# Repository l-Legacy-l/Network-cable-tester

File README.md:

# Network-cable-tester
This project was carried out in the first year of a bachelor's degree in computer science at the Haute école en Hainaut.

The purpose of the project is to check the operating status of a network cable (RJ45).
The cable tester includes the LED module and the PIC module. 
2 versions of the PCB have been made, the first one allows to be engraved only in single layer and the second one in double layer (space saving) .

In terms of PIC programming (PIC16F628A), 3 modes have been implemented: 
1. a short press of the button switches to the next LED
2. a long press speeds up the process by automatically switching to the following LED
3. a longer press lights up all the LEDs at the same time

# Usage

You can test the project with the Proteus simulation software and the right cabling.

You can also try it in real with a breadboard, the right hardware and MPlab software to upload the code into the PIC.

You must use the compiled file NetworkCableTester.hex

For more information, you can consult the report detailing the software and hardware used and more detailed explanations (in French).

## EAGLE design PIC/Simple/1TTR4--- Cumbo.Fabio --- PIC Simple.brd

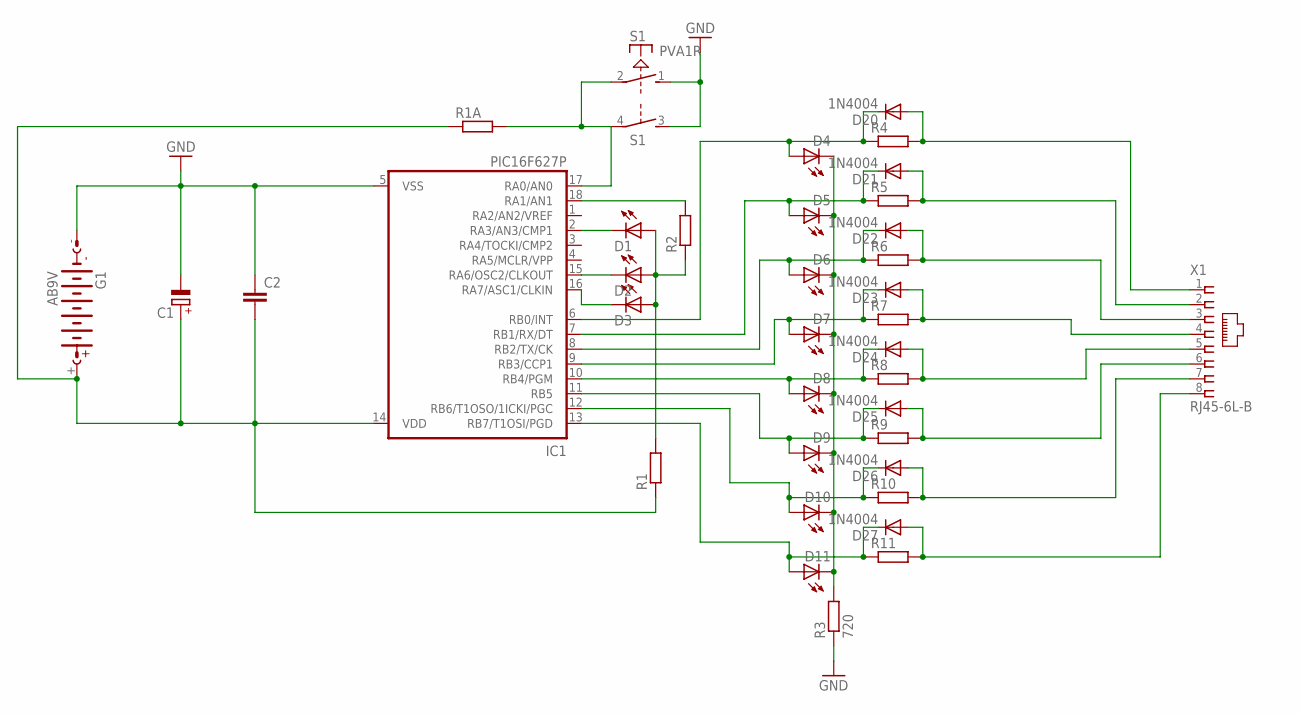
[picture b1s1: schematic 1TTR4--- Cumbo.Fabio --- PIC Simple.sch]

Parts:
C1: CPOL-EUE5-6; E5-6
C2: C-EU050-024X044; C050-024X044
D1, D2, D3, D4, D5, D6, D7, D8, D9, D10, D11: LED5MM
D20, D21, D22, D23, D24, D25, D26, D27: 1N4004; DO41-10
G1: AB9V
IC1: PIC16F627P; DIL18
R1, R1A, R2, R4, R5, R6, R7, R8, R9, R10, R11: R-EU_0204/7; 0204/7
R3: 720; 0204/7
S1: PVA1R
X1: RJ45-6L-B; RJ45-NO-SHIELD

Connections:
GND: C1.-, C2.1, G1.-, IC1.5 (VSS), R3.1, S1.1 (S), S1.3 (S)
unnamed: D11.A, D27.C, IC1.13 (RB7/T1OSI/PGD), R11.1
unnamed: D27.A, R11.2, X1.8
unnamed: D10.A, D26.C, IC1.12 (RB6/T1OSO/1ICKI/PGC), R10.1
unnamed: D9.A, D25.C, IC1.11 (RB5), R9.1
unnamed: D24.A, R8.2, X1.5
unnamed: D23.A, R7.2, X1.4
unnamed: D22.A, R6.2, X1.3
unnamed: D21.A, R5.2, X1.2
unnamed: D20.A, R4.2, X1.1
unnamed: D1.K (C), IC1.2 (RA3/AN3/CMP1)
unnamed: D25.A, R9.2, X1.6
unnamed: D7.A, D23.C, IC1.9 (RB3/CCP1), R7.1
unnamed: D26.A, R10.2, X1.7
unnamed: D6.A, D22.C, IC1.8 (RB2/TX/CK), R6.1
unnamed: D5.A, D21.C, IC1.7 (RB1/RX/DT), R5.1
unnamed: D4.A, D20.C, IC1.6 (RB0/INT), R4.1
unnamed: D4.K (C), D5.K (C), D6.K (C), D7.K (C), D8.K (C), D9.K (C), D10.K (C), D11.K (C), R3.2
unnamed: C1.+, C2.2, G1.+, IC1.14 (VDD), R1.1, R1A.1
unnamed: IC1.17 (RA0/AN0), R1A.2, S1.2, S1.4
unnamed: D8.A, D24.C, IC1.10 (RB4/PGM), R8.1
unnamed: D3.K (C), IC1.16 (RA7/ASC1/CLKIN)
unnamed: D2.K (C), IC1.15 (RA6/OSC2/CLKOUT)
unnamed: IC1.18 (RA1/AN1), R2.2
unnamed: D1.A, D2.A, D3.A, R1.2, R2.1

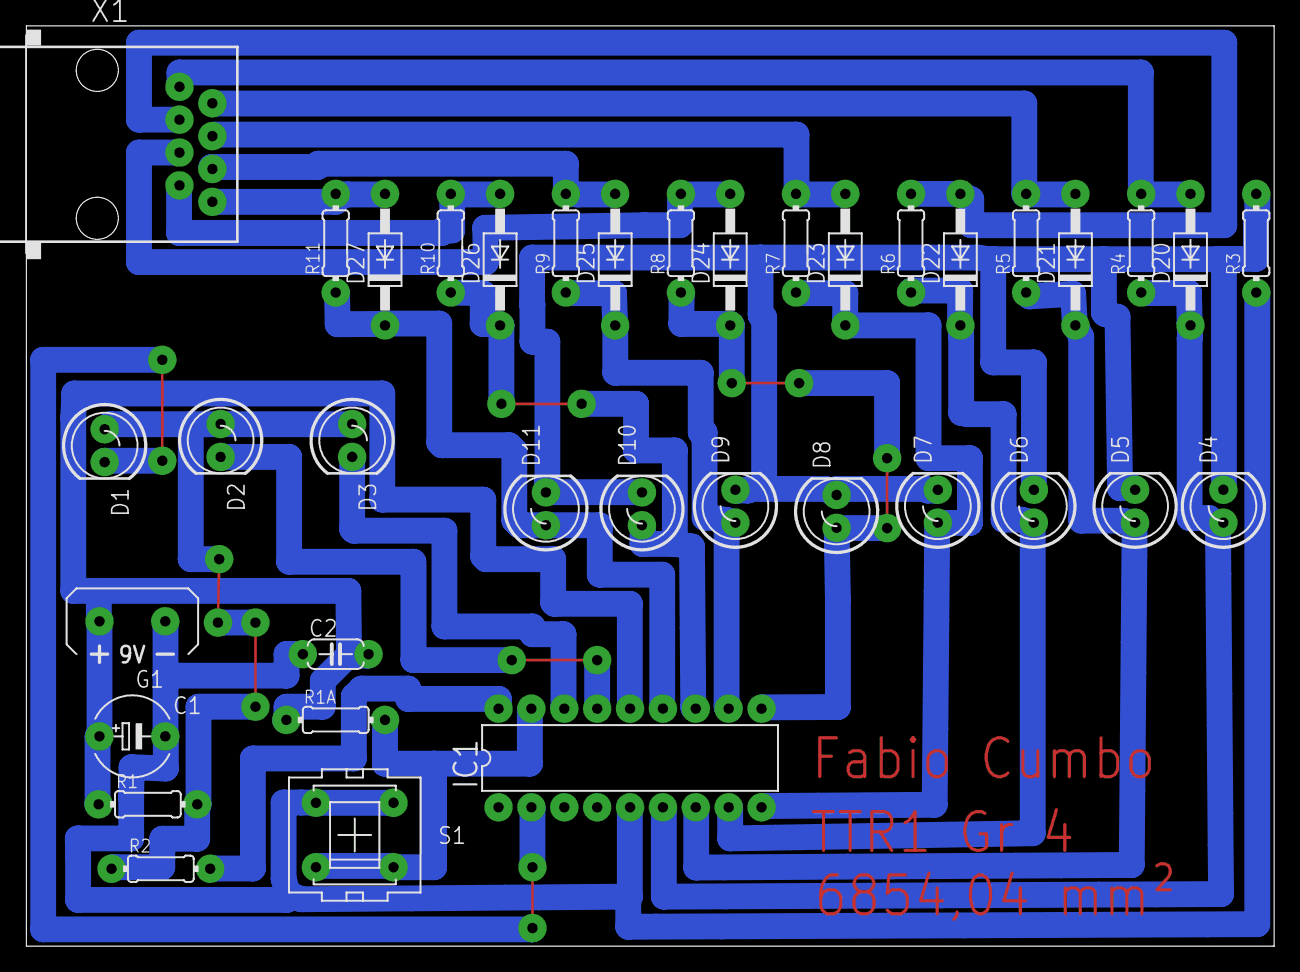
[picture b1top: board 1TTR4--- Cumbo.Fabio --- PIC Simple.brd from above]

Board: 2 copper layers, 96.4 x 71.1 mm, 37 parts (0 on the bottom side), 25 nets.

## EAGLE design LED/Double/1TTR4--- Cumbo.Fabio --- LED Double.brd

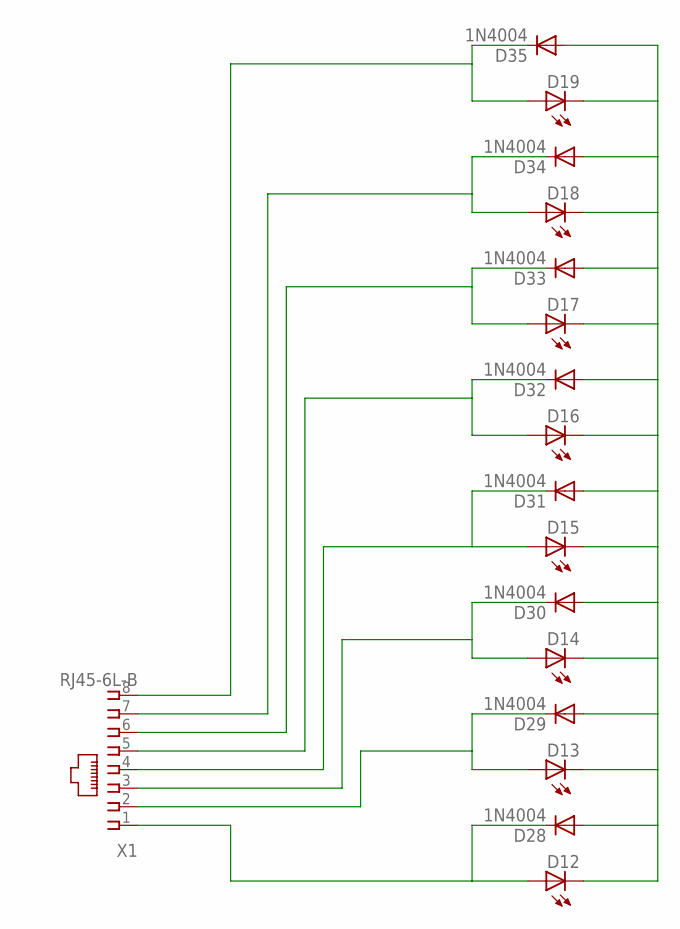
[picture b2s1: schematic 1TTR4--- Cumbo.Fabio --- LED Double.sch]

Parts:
D12, D13, D14, D15, D16, D17, D18, D19: LED5MM
D28, D29, D30, D31, D32, D33, D34, D35: 1N4004; DO41-10
X1: RJ45-6L-B; RJ45-NO-SHIELD

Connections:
unnamed: D12.A, D28.C, X1.1
unnamed: D12.K (C), D13.K (C), D14.K (C), D15.K (C), D16.K (C), D17.K (C), D18.K (C), D19.K (C), D28.A, D29.A, D30.A, D31.A, D32.A, D33.A, D34.A, D35.A
unnamed: D13.A, D29.C, X1.2
unnamed: D14.A, D30.C, X1.3
unnamed: D15.A, D31.C, X1.4
unnamed: D16.A, D32.C, X1.5
unnamed: D17.A, D33.C, X1.6
unnamed: D18.A, D34.C, X1.7
unnamed: D19.A, D35.C, X1.8

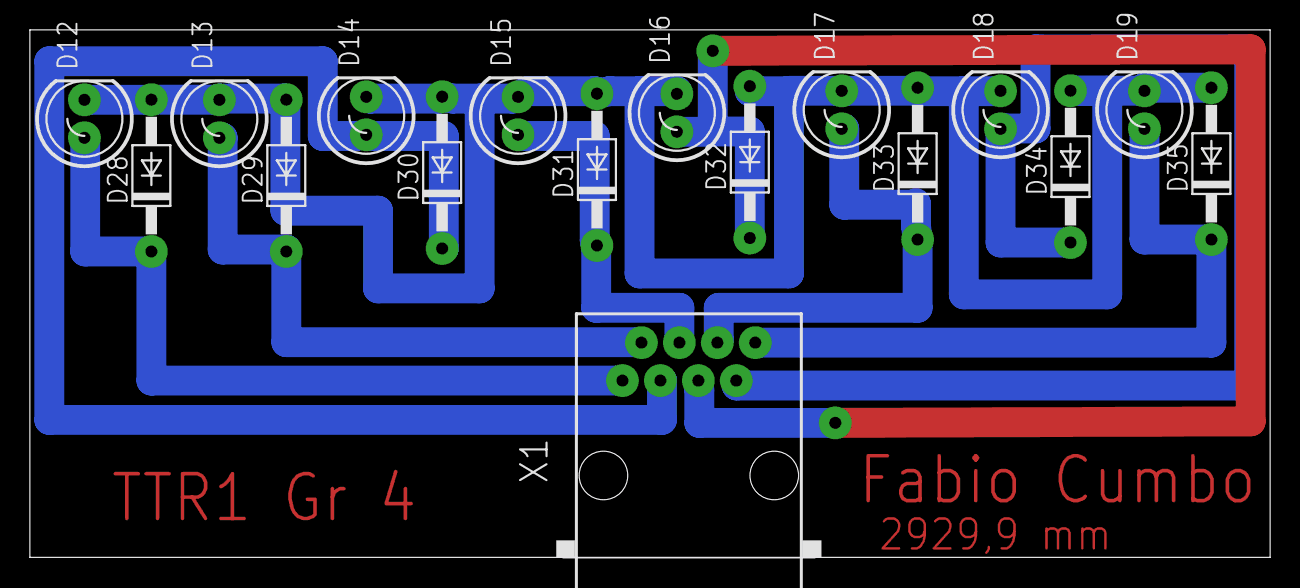
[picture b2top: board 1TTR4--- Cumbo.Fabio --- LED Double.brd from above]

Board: 2 copper layers, 83.0 x 35.3 mm, 17 parts (0 on the bottom side), 9 nets.

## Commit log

2018-09-21 Ajout du projet complet
